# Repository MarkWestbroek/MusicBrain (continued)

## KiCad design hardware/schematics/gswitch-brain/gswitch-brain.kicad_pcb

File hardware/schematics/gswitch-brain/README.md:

# gswitch-brain — ESP32-S3-hoofdbord (Guitar Effect Switcher)

**Status**: rev 0.1 geroute — ERC 0, netcheck OK, DRC 0/0 (2026-07-12).
**Nog niet bestellen**: eerst `jlc_fix.py`-LCSC-match + fab-pakket + review.
Leidende spec: [`doc/guitar-switcher-spec.md`](../../../doc/guitar-switcher-spec.md).

*(Regenereren: `python hardware/kicad-generators/board_overview.py
<pcb> gswitch-brain-overzicht.json` — 3D-render via kicad-cli met
callouts in bord-mm.)*

## Wat dit bord is

Het "moederbord" van de switcher: ESP32-S3-WROOM-**1U** (U.FL-antenne →
SMA-bulkhead op de stalen kast), 12V **center-negatief** in (omkeer-P-FET +
polyfuse + SMAJ15A), buck 12→5V (TPS563201), AMS1117-3.3, USB-C voor
flash/debug (SS34-diode naar de 5V-rail: bord draait op USB zonder 12V),
MIDI-DIN in (H11L1) + uit (74HCT14-buffer op 5V), en 2× chain-poort
(74HCT541 → RJ45, met 100R-serieweerstanden en 10k/15k-spanningsdelers
voor de DATA_RET-teruglezing).

- Bord: 100 × 70 mm, 2-laags, GND-vlakken beide zijden.
- Randen: west DC + USB-C + debug-UART; noord 2× MIDI-DIN; zuid 2× RJ45;
  oost module + headers (OLED-I²C, 4 knoppen, encoder, 8× spare-GPIO).
- RESET- en BOOT-tactschakelaars naast de module; status-LED (IO42).

## GPIO-toewijzing (firmware-contract)

| Functie | GPIO | | Functie | GPIO |
|---|---|---|---|---|
| Chain A CLK/DATA/LATCH/EN | 4/5/6/7 | | I²C SDA/SCL | 10/13 |
| Chain B CLK/DATA/LATCH/EN | 15/16/17/18 | | MIDI RX/TX | 11/12 |
| DATA_RET A / B (in, 3V-deler) | 8 / 9 | | Knoppen 1-4 | 35/36/37/38 |
| Encoder A/B/SW | 39/40/41 | | Status-LED | 42 |
| Spare-header | 21/14/47/48/1/2 | | Debug-UART | 43/44 |

Strapping-pinnen IO0/IO3/IO45/IO46 zijn vrijgehouden (IO0 = BOOT-knop).

## Connector-pinouts

**J10/J11 — chain A/B (RJ45, naar loop8-borden).** ⚠️ Géén ethernet:
pin 4 voert 12 V!

| pin | 1 | 2 | 3 | 4 | 5 | 6 | 7 | 8 | scherm |
|---|---|---|---|---|---|---|---|---|---|
| functie | CLK | GND | DATA | **+12V** | GND | DRET (terug) | LATCH | EN | GND |

**J3 — MIDI UIT / J4 — MIDI IN (DIN-5, 180°).**

| DIN-pin | J3 (uit) | J4 (in) |
|---|---|---|
| 4 | +5V via 220R | stroomlus → H11L1 (220R) |
| 5 | data via 220R (HCT14-buffer) | stroomlus → H11L1 |
| 2 | GND | n.c. (galvanisch gescheiden) |
| scherm (E) | GND | GND |

**Headers (oostrand + debug).** Alle logica op de headers is 3,3 V.

| conn. | pin 1 → n |
|---|---|
| J5 OLED | GND · +3V3 · SCL · SDA |
| J6 knoppen | BTN1 · BTN2 · BTN3 · BTN4 · GND |
| J7 encoder | ENC_A · GND · ENC_B · ENC_SW · GND |
| J8 spare | +3V3 · GND · SPARE1…SPARE6 |
| J9 debug-UART | TX · RX · GND |

**J1 — voeding (2,1 mm barrel):** center = **GND**, mantel = +12 V
(center-negatief, pedaalconventie); ompoolbeveiligd (P-FET) en
polyfuse + TVS.

Diagrammen van álle connectoren staan in [`pinouts/`](pinouts/)
(gegenereerd met `pinout_svg.py` — leest netten uit het bordbestand,
loopt dus nooit uit de pas met het ontwerp).

## Onderdelen-notities

- **Module**: ESP32-S3-WROOM-**1U**-N8R2 — de -1U (U.FL) is verplicht in de
  metalen kast. EP-thermal-vias (0,2 mm) zijn uit de lib-footprint gefilterd
  (onder JLC-minimumboring); EP soldeert op het vlak.
- **MIDI-DIN**: CUI SDS-50J (footprint uit de maattekening, zie
  `doc/data-sheets/`-werkwijze). MIDI-out op 5V met 2×220R (spec-conform).
- **RJ45**: zelfde "56-klasse" afgeschermde 8P8C als loop8; schermen → GND
  (de brain is het sterpunt van de besturingsketen).
- **DC**: 2,1 mm barrel, **center-negatief** (pedaalconventie!).
- **Buck**: TPS563201 (SOT-23-6) + SRN4018 4,7 µH; FB 56k/10k (≈5,07 V);
  EN-deler 100k/33k vanaf 12V.
- **BOM/LCSC**: nog geen LCSC-velden — `jlc_fix.py` vóór fab-run.

## Bouwen

Zelfde pijplijn als loop8: `gen_gswitch_brain.py` → ERC/netcheck/DRC →
`export_dsn` → `gswitch_dsn_prep.py <dsn> --no-keepout --clearance-150` →
freerouting → generator opnieuw (SES native) → gnd_stitch/gnd_bridge → DRC 0/0.

### Routing-opbouw (rev 0.1)

- **Hand** (permanent geskipt bij SES-apply): +12V-ruggegraat, +3V3-snelweg
  (B, y=158,9), USB DP/DM/VBUS (bondlusjes + lanen, usb-netclass 0,1/0,15),
  CC2 (B-duik naast de DM-jog), en de **F-bus U2.7/8/9 → module p9/p10/p11**
  (B_DATA/B_LATCH/B_EN): lanen noord van de SW1/SW2-padrand, schuine
  eindstukjes de pads in.
- **Freerouting**: hoofdronde (r6) + hybride naruns (`--narun=<netten>` in
  `gswitch_dsn_prep.py`) voor netten die de hoofdronde niet haalde. De
  narun-SES wordt met `only=NARUN_NETS` over de hoofdronde gelegd.
- **GND**: 15 hand-stitchvia's + `gnd_stitch.json` (9 auto + 1 brugvia);
  de laatste brugplek is met een polygon-doorsnede (B-flard × F-hoofdvlak)
  bepaald op (163,78, 123,43).

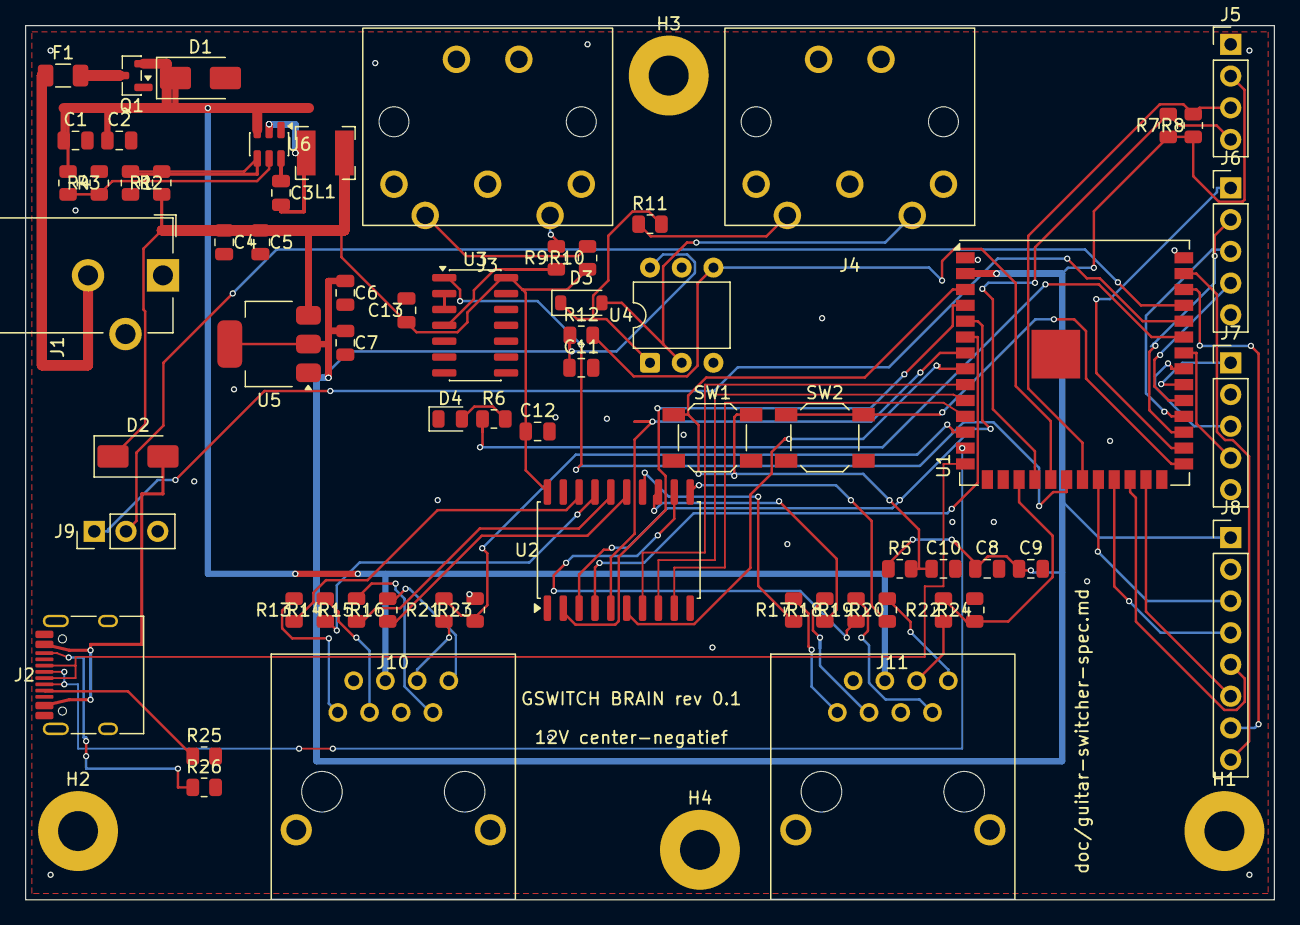
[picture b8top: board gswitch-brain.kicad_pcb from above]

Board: 2 copper layers, 100.0 x 70.0 mm, 69 parts (0 on the bottom side), 73 nets.

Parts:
C1: 10u; C_0805_2012Metric
C2, C3, C7, C9, C11, C12, C13: 100n; C_0805_2012Metric
C4, C5, C6, C8: 22u; C_0805_2012Metric
C10: 1u; C_0805_2012Metric
D1: SMAJ15A; D_SMA
D2: SS34; D_SMA
D3: 1N4148W; D_SOD-123
D4: LED-GN; LED_0805_2012Metric
F1: 1.1A; Fuse_1206_3216Metric
H1, H2, H3, H4: M3; MountingHole_3.2mm_M3_Pad
J1: DC-12V; BarrelJack_CUI_PJ-102AH_Horizontal
J2: USB-C; USB_C_Receptacle_HRO_TYPE-C-31-M-12
J3, J4: SDS-50J; DIN5_SDS50J
J5: OLED-I2C; PinHeader_1x04_P2.54mm_Vertical
J6: KNOPPEN; PinHeader_1x05_P2.54mm_Vertical
J7: ENCODER; PinHeader_1x05_P2.54mm_Vertical
J8: SPARE; PinHeader_1x08_P2.54mm_Vertical
J9: DEBUG; PinHeader_1x03_P2.54mm_Vertical
J10, J11: RJ45-S; RJ45_shielded
L1: 4u7; L_Bourns-SRN4018
Q1: AO3401; SOT-23
R1: 56k; R_0805_2012Metric
R2, R5, R21, R22: 10k; R_0805_2012Metric
R3: 100k; R_0805_2012Metric
R4: 33k; R_0805_2012Metric
R6, R12: 1k; R_0805_2012Metric
R7, R8: 4k7; R_0805_2012Metric
R9, R10, R11: 220R; R_0805_2012Metric
R13, R14, R15, R16, R17, R18, R19, R20: 100R; R_0805_2012Metric
R23, R24: 15k; R_0805_2012Metric
R25, R26: 5k1; R_0805_2012Metric
SW1: RESET; SW_SPST_SKQG_WithStem
SW2: BOOT; SW_SPST_SKQG_WithStem
U1: ESP32-S3-WROOM-1U-N8R2; ESP32-S3-WROOM-1U
U2: 74HCT541; SOIC-20W_7.5x12.8mm_P1.27mm
U3: 74HCT14; SOIC-14_3.9x8.7mm_P1.27mm
U4: H11L1; DIP-6_W7.62mm
U5: AMS1117-3.3; SOT-223-3_TabPin2
U6: TPS563201; SOT-23-6

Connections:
+3V3: C6.1, C7.1, C8.1, C9.1, C11.1, J5.2, J8.1, R5.1, R7.1, R8.1, R12.1, U1.2, U4.6, U5.2
+5V: C4.1, C5.1, C12.1, C13.1, D2.1, L1.2, R1.1, R10.1, U2.20, U3.14, U5.3
+12V: C1.1, C2.1, D1.1, J10.4, J11.4, Q1.2, R3.1, U6.3
/+12VRAW: F1.1, J1.2
/A_CLK: U1.4, U2.2
/A_CLK5: R13.1, U2.18
/A_CLKJ: J10.1, R13.2
/A_DATA: U1.5, U2.3
/A_DATA5: R14.1, U2.17
/A_DATAJ: J10.3, R14.2
/A_DRETJ: J10.6, R21.1
/A_EN: U1.7, U2.5
/A_EN5: R16.1, U2.15
/A_ENJ: J10.8, R16.2
/A_LATCH: U1.6, U2.4
/A_LATCH5: R15.1, U2.16
/A_LATCHJ: J10.7, R15.2
/BCK_EN: R3.2, R4.1, U6.5
/BOOT: SW2.1, U1.27
/BST: C3.1, U6.6
/BTN1: J6.1, U1.28
/BTN2: J6.2, U1.29
/BTN3: J6.3, U1.30
/BTN4: J6.4, U1.31
/B_CLK: U1.8, U2.6
/B_CLK5: R17.1, U2.14
/B_CLKJ: J11.1, R17.2
/B_DATA: U1.9, U2.7
/B_DATA5: R18.1, U2.13
/B_DATAJ: J11.3, R18.2
/B_DRETJ: J11.6, R22.1
/B_EN: U1.11, U2.9
/B_EN5: R20.1, U2.11
/B_ENJ: J11.8, R20.2
/B_LATCH: U1.10, U2.8
/B_LATCH5: R19.1, U2.12
/B_LATCHJ: J11.7, R19.2
/CC1: J2.A5, R25.1
/CC2: J2.B5, R26.1
/DBG_RX: J9.2, U1.37
/DBG_TX: J9.1, U1.36
/DRET_A: R21.2, R23.1, U1.12
/DRET_B: R22.2, R24.1, U1.17
/ENC_A: J7.1, U1.32
/ENC_B: J7.3, U1.33
/ENC_SW: J7.4, U1.34
/ESP_EN: C10.1, R5.2, SW1.1, U1.3
/FB: R1.2, R2.1, U6.4
/LEDK: D4.2, R6.2
/LEDK_A: R6.1, U1.35
/MIDI_RX: R12.2, U1.19, U4.4
/MIDI_TX: U1.20, U3.1
/MIN4: J4.4, R11.1
/MIN5: D3.2, J4.5, U4.2
/MINA: D3.1, R11.2, U4.1
/MOUT4: J3.4, R10.2
/MOUT5: J3.5, R9.2
/MTX5: R9.1, U3.4
/MTXN: U3.2, U3.3
/RAWF: F1.2, Q1.3
/SCL: J5.3, R8.2, U1.21
/SDA: J5.4, R7.2, U1.18
/SPARE1: J8.3, U1.22
/SPARE2: J8.4, U1.23
/SPARE3: J8.5, U1.24
/SPARE4: J8.6, U1.25
/SPARE5: J8.7, U1.38
/SPARE6: J8.8, U1.39
/SW: C3.2, L1.1, U6.2
/USB_DM: J2.A7, J2.B7, U1.13
/USB_DP: J2.A6, J2.B6, U1.14
/VBUS: D2.2, J2.A4, J2.A9, J2.B4, J2.B9
GND: C1.2, C2.2, C4.2, C5.2, C6.2, C7.2, C8.2, C9.2, C10.2, C11.2, C12.2, C13.2, D1.2, D4.1, H1.1, H2.1, H3.1, H4.1, J1.1, J2.A1, J2.A12, J2.B1, J2.B12, J2.SH, J3.2, J3.E, J4.E, J5.1, J6.5, J7.2, J7.5, J8.2, J9.3, J10.2, J10.5, J10.SH, J11.2, J11.5, J11.SH, Q1.1, R2.2, R4.2, R23.2, R24.2, R25.2, R26.2, SW1.2, SW2.2, U1.1, U1.40, U1.41, U2.1, U2.10, U2.19, U3.5, U3.7, U3.9, U3.11, U3.13, U4.5, U5.1, U6.1

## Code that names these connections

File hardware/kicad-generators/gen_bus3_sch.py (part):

"""Generate musicbrain-busboard.kicad_sch — v3 per doc/busboard-v3-plan.md.

v3 t.o.v. v2 (gen 2): slots 2x12 (audio-lijnen MCLK/BCLK/LRCLK gedeeld +
I2SD1-6 per slot, CONVST=pin 19), audiohub J24 (2x7), MIDI 2xIN/2xUIT (J22 =
TX7), USB-host-doorvoer J23 (2x5, volgorde-ongevoelig 1-op-1), R-78E5.0-1.0.
Verder v2-architectuur: 74HC154-CS-decoder, 74HC165-IRQ-keten, expansie J21,
CAN3, codec-header J17, TUNE-IN, delegate-UARTs.
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
# ---- v2-pintoewijzing (zie doc/busboard-v2-plan.md) ----
# links: symboolpin 2..24 = D0..D12? (2=D0,3=D1,4=D2,...,14=D12,16=D24..24=D32)
tpin_label(2, "DISP_CS")    # D0
tpin_label(3, "TUNE_T")     # D1  <- schmitt-uitgang TUNE
tpin_label(4, "LDAC")       # D2
tpin_label(5, "CSA0")       # D3
tpin_label(6, "CSA1")       # D4
tpin_label(7, "CSA2")       # D5
tpin_label(8, "CSA3")       # D6
tpin_label(9, "I2S_OUT")    # D7  OUT1A -> codec DIN
tpin_label(10, "I2S_IN")    # D8  IN1  <- codec DOUT
tpin_label(11, "CS_EN")     # D9  /E0 decoder
tpin_label(12, "D10")       # D10 vrij -> EXP
# 13 = MOSI via R2 (onder), 14 = MISO
tpin_label(14, "MISO")
tpin_label(16, "DISP_DC")   # D24
tpin_label(17, "DISP_RST")  # D25
tpin_label(18, "MOSI1")     # D26
tpin_label(19, "SCK1")      # D27
tpin_label(20, "MIDI_RX2")  # D28 RX7
tpin_label(21, "MIDI_TX2")  # D29 TX7 -> MIDI OUT2 (v3)
tpin_label(22, "CAN_RX")    # D30 CRX3
tpin_label(23, "CAN_TX")    # D31 CTX3
tpin_label(24, "D32")       # D32 vrij -> EXP
# rechts: 25=D33 ... 33=D41, 35=D13, 36..45=D14..D23
tpin_label(25, "D33")       # D33 vrij -> EXP
tpin_label(26, "MIDI_RX1")  # D34 RX8
tpin_label(27, "MIDI_TX")   # D35 TX8
tpin_label(28, "D36")
tpin_label(29, "D37")
tpin_label(30, "D38")
tpin_label(31, "D39")
tpin_label(32, "CONVST")    # D40 CONVST (busbrede sample-strobe, slotpin 19)
tpin_label(33, "SPARE2")    # D41 ADC_RESET
tpin_label(36, "DLG1_TX")   # D14 TX3
tpin_label(37, "DLG1_RX")   # D15 RX3
tpin_label(38, "DLG2_TX")   # D16 TX4
tpin_label(39, "DLG2_RX")   # D17 RX4
tpin_label(40, "SDA")       # D18
tpin_label(41, "SCL")       # D19
tpin_label(42, "LRCLK")     # D20 (busnet, slotpin 23)
tpin_label(43, "BCLK")      # D21 (busnet, slotpin 22)
tpin_label(44, "CODEC_RST") # D22 -> codec-header (bovenaan kolom)
tpin_label(45, "MCLK")      # D23 (busnet, slotpin 21)

# series R: MOSI (pin13, links) en SCLK (pin35, rechts)
x, y, _ = TEENSY_PINS[13]
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     ("17", "Y15", "output")]))
place_box("74HC154", "U4", "74HC154", 155, 62,
          "Package_SO:SOIC-24W_7.5x15.4mm_P1.27mm",
          {"23": ("label", "CSA0"), "22": ("label", "CSA1"),
           "21": ("label", "CSA2"), "20": ("label", "CSA3"),
           "18": ("label", "CS_EN"), "19": ("power", "power:GND"),
           "24": ("power", "power:+3V3"), "12": ("power", "power:GND"),
           "1": ("label", "CS1"), "2": ("label", "CS2"), "3": ("label", "CS3"),
           "4": ("label", "CS4"), "5": ("label", "CS5"), "6": ("label", "CS6"),
           "7": ("label", "CS7"), "8": ("label", "CS8"), "9": ("label", "CS9"),
           "10": ("label", "CS10"), "11": ("label", "CS11"), "13": ("label", "CS12"),
           "14": ("label", "CS13"), "15": ("label", "CS14"),
           "16": ("label", "IRQSTAT"), "17": ("nc",)})
cap100n("C10", 128, 62)

# ============ v2: IRQ-keten 2x 74HC165 + 1G125 ============
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place_box("74HC165", "U5", "74HC165", 200, 62,
          "Package_SO:SOIC-16_3.9x9.9mm_P1.27mm",
          {"1": ("label", "PL"), "2": ("label", "SCLK"),
           "15": ("power", "power:GND"), "10": ("label", "CHAIN"),
           "16": ("power", "power:+3V3"), "8": ("power", "power:GND"),
           "6": ("label", "IRQ5"), "5": ("label", "IRQ6"), "4": ("power", "power:GND"),
           "3": ("power", "power:GND"), "14": ("label", "IRQ1"), "13": ("label", "IRQ2"),
           "12": ("label", "IRQ3"), "11": ("label", "IRQ4"),
           "9": ("label", "Q7A"), "7": ("nc",)})
# U6 = tweede byte: IRQ7..IRQ12 (expansie) op D7..D2 — eigen ~PL-RC (PL2),
# zodat de puls lokaal bij U6 (noordstrook) wordt opgewekt i.p.v. het halve
# bord over te reizen; beide RC's hangen aan dezelfde IRQSTAT-flank.
place_box("74HC165", "U6", "74HC165", 200, 120,
          "Package_SO:SOIC-16_3.9x9.9mm_P1.27mm",
          {"1": ("label", "PL2"), "2": ("label", "SCLK"),
           "15": ("power", "power:GND"), "10": ("power", "power:GND"),
           "16": ("power", "power:+3V3"), "8": ("power", "power:GND"),
           "6": ("label", "IRQ7"), "5": ("label", "IRQ8"), "4": ("label", "IRQ9"),
           "3": ("label", "IRQ10"), "14": ("label", "IRQ11"), "13": ("label", "IRQ12"),
           "12": ("power", "power:GND"), "11": ("power", "power:GND"),
           "9": ("label", "CHAIN"), "7": ("nc",)})
libs_extra.append(boxdef("74LVC1G125",
    [("1", "~{OE}", "input"), ("2", "A", "input"),
     ("5", "VCC", "power_in"), ("3", "GND", "power_in")],
    [("4", "Y", "tri_state")], width=12.7))
place_box("74LVC1G125", "U7", "74LVC1G125", 155, 120,
          "Package_TO_SOT_SMD:SOT-23-5",
          {"1": ("label", "IRQSTAT"), "2": ("label", "Q7A"),
           "5": ("power", "power:+3V3"), "3": ("power", "power:GND"),
           "4": ("label", "MISO")})
cap100n("C15", 178, 62)   # U5
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cap100n("C17", 140, 120)  # U7/1G17's
# PL-RC (gatein8-recept): C9 220p vanaf IRQSTAT, R5 10k pull-up naar 3V3
(c9a, c9b) = rcomp("C9", "220p", 128, 138, 90)
wire(*c9a, c9a[0] - 3.81, c9a[1]); label("IRQSTAT", c9a[0] - 3.81, c9a[1])
wire(*c9b, c9b[0] + 3.81, c9b[1]); label("PL", c9b[0] + 3.81, c9b[1])
(r5t, r5b) = rcomp("R5", "10k", 128, 122, 0)
power("power:+3V3", *r5t)
wire(*r5b, r5b[0], r5b[1] + 2.54); label("PL", r5b[0], r5b[1] + 2.54)
# tweede PL-RC voor U6 (PL2)
(c18a, c18b) = rcomp("C18", "220p", 155, 138, 90)
wire(*c18a, c18a[0] - 3.81, c18a[1]); label("IRQSTAT", c18a[0] - 3.81, c18a[1])
wire(*c18b, c18b[0] + 3.81, c18b[1]); label("PL2", c18b[0] + 3.81, c18b[1])
(r33t, r33b) = rcomp("R33", "10k", 155, 122, 0)
power("power:+3V3", *r33t)
wire(*r33b, r33b[0], r33b[1] + 2.54); label("PL2", r33b[0], r33b[1] + 2.54)
# IRQ-pulldowns (12x 100k): gedefinieerd niveau voor lege slots/expansie
for k in range(12):
    xr = 88 + 5.08 * k
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          "Package_SO:SOIC-20W_7.5x12.8mm_P1.27mm",
          {"1": ("power", "power:+3V3"), "19": ("power", "power:GND"),
           "20": ("power", "power:+3V3"), "10": ("power", "power:GND"),
           "2": ("label", "SCLK"), "3": ("label", "MOSI"), "4": ("label", "LDAC"),
           "5": ("label", "CONVST"), "6": ("label", "SPARE2"),
           "7": ("power", "power:GND"), "8": ("power", "power:GND"),
           "9": ("power", "power:GND"),
           "18": ("label", "XSCLK0"), "17": ("label", "XMOSI0"),
           "16": ("label", "XLDAC0"), "15": ("label", "XCONVST0"),
           "14": ("label", "XRST0"), "13": ("nc",), "12": ("nc",), "11": ("nc",)})
cap100n("C11", 222, 100)
# 33R serie in de gebufferde lijnen naar de expansieheader
for k, (a, b) in enumerate((("XSCLK0", "XSCLK"), ("XMOSI0", "XMOSI"),
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
# MIDI OUT: 1G17-buffer + 10R/33R per 3V3-MIDI-spec
place_box("74LVC1G17", "U11", "74LVC1G17", 392, 158, "Package_TO_SOT_SMD:SOT-23-5",
          {"2": ("label", "MIDI_TX"), "5": ("power", "power:+3V3"),
           "3": ("power", "power:GND"), "4": ("label", "MOUT_Y"), "1": ("nc",)})
(l, r) = rcomp("R10", "10R", 414, 152, 90)
wire(*l, l[0] - 2.54, l[1]); label("MOUT_Y", l[0] - 2.54, l[1])
wire(*r, r[0] + 2.54, r[1]); label("MOUT5", r[0] + 2.54, r[1])
(l, r) = rcomp("R11", "33R", 414, 160, 90)
power("power:+3V3", l[0] - 1.27, l[1], vx=l[0] - 1.27, vy=l[1] - 3.302)
wire(*l, l[0] - 1.27, l[1])
wire(*r, r[0] + 2.54, r[1]); label("MOUT4", r[0] + 2.54, r[1])
component("Custom:Conn_01x03", "J15", "MIDI OUT", 438, 160, 0,
          "Connector_PinHeader_2.54mm:PinHeader_1x03_P2.54mm_Vertical",
          extra_props=rprop("J15", "MIDI OUT", 438, 160, 438, 160 - 6.35, 438, 160 + 6.35))
wire(430.38, 157.46, 425.3, 157.46); label("MOUT5", 425.3, 157.46)
wire(430.38, 160, 425.3, 160); label("MOUT4", 425.3, 160)
wire(430.38, 162.54, 427.84, 162.54); power("power:GND", 427.84, 162.54)

# ============ v3: MIDI OUT2 (TX7 -> 1G17 -> J22) ============
place_box("74LVC1G17", "U14", "74LVC1G17", 392, 182, "Package_TO_SOT_SMD:SOT-23-5",
          {"2": ("label", "MIDI_TX2"), "5": ("power", "power:+3V3"),
           "3": ("power", "power:GND"), "4": ("label", "MOUT2_Y"), "1": ("nc",)})
(l, r) = rcomp("R34", "10R", 414, 176, 90)
wire(*l, l[0] - 2.54, l[1]); label("MOUT2_Y", l[0] - 2.54, l[1])
wire(*r, r[0] + 2.54, r[1]); label("MOUT2_5", r[0] + 2.54, r[1])
(l, r) = rcomp("R35", "33R", 414, 184, 90)
power("power:+3V3", l[0] - 1.27, l[1], vx=l[0] - 1.27, vy=l[1] - 3.302)
wire(*l, l[0] - 1.27, l[1])
wire(*r, r[0] + 2.54, r[1]); label("MOUT2_4", r[0] + 2.54, r[1])
component("Custom:Conn_01x03", "J22", "MIDI OUT2", 438, 184, 0,
          "Connector_PinHeader_2.54mm:PinHeader_1x03_P2.54mm_Vertical",
          extra_props=rprop("J22", "MIDI OUT2", 438, 184, 438, 184 - 6.35, 438, 184 + 6.35))
wire(430.38, 181.46, 425.3, 181.46); label("MOUT2_5", 425.3, 181.46)
wire(430.38, 184, 425.3, 184); label("MOUT2_4", 425.3, 184)
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
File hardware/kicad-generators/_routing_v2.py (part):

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    jx, jy = P['J21'][jpin]
    ry = CS_ROWY_[net]
    T(net, 'F.Cu', SW, (colx, ry), (jx, ry), (jx, jy))
# IRQSTAT: pin16 -> kanaalkolom x 43.9 (F, met B-hop over de DISP-rijen heen
# voor de noordtak) -> C9 + U7 (zuid) en C18 (noordoost)
px, py = P['U4']['16']
T('/IRQSTAT', 'F.Cu', SW, (px, py), (43.9, py), (43.9, 92.5),
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  (P['R5']['2'][0], 94.6), (P['R5']['2'][0], P['R5']['2'][1]))
T('/PL', 'F.Cu', SW, (P['C9']['2'][0], 94.6), (P['U5']['1'][0], 94.6),
  (P['U5']['1'][0], P['U5']['1'][1]))
# PL2: C18.2 + R33.2 -> U6 pin1
T('/PL2', 'F.Cu', SW, (P['C18']['2'][0], P['C18']['2'][1]),
  (P['R33']['2'][0], P['C18']['2'][1]), (P['R33']['2'][0], P['R33']['2'][1]))
T('/PL2', 'F.Cu', SW, (P['R33']['2'][0], P['R33']['2'][1]),
  (P['U6']['1'][0], P['R33']['2'][1]), (P['U6']['1'][0], P['U6']['1'][1]))

# ---- IRQ-keten zuidwest ----
# IRQ1-4: zuidrij-pinnen (3-6) recht omhoog naar hun lane
for net, pin in (('/IRQ1', '6'), ('/IRQ2', '5'), ('/IRQ3', '4'), ('/IRQ4', '3')):
    px, py = P['U5'][pin]
    T(net, 'F.Cu', SW, (px, py), (px, lane_y(net)))
    V(net, px, lane_y(net))
# IRQ5/6: noordrij-pinnen (14/13) via pad-gap-kolommen x 33.2 / 34.465
T('/IRQ5', 'F.Cu', SW, (P['U5']['14'][0], P['U5']['14'][1]), (P['U5']['14'][0], 97.5),
  (33.2, 97.5), (33.2, lane_y('/IRQ5')))
V('/IRQ5', 33.2, lane_y('/IRQ5'))
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    p1 = P[ref]['1']
    T(net, 'F.Cu', SW, (colx, 103.7 if colx > 34.6 else lane_y(net)),
      (colx, p1[1] - 0.55), (p1[0], p1[1]))
# Q7A: U5 pin9 -> rij y 96.9 -> kolom x 46.6 -> rij y 85 -> U7 pin2
T('/Q7A', 'F.Cu', SW, (P['U5']['9'][0], P['U5']['9'][1]), (P['U5']['9'][0], 96.9),
  (46.6, 96.9), (46.6, 85.0), (P['U7']['2'][0], 85.0), (P['U7']['2'][0], P['U7']['2'][1]))
# CHAIN: U6 pin10 -> F-rij y 18.3 -> kanaal (B/F-hops) -> U5 pin10
T('/CHAIN', 'F.Cu', SW, (P['U6']['10'][0], P['U6']['10'][1]), (P['U6']['10'][0], 18.3),
  (41.89, 18.3), (41.89, 26.0))
V('/CHAIN', 41.89, 26.0)
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    ly = lane_y(net)
    T(net, 'F.Cu', SW, (colx, ly), (colx, rowy), (px, rowy), (px, py))
    V(net, colx, ly)
XPINS = [('/XSCLK0', '18', 'R16', '/XSCLK', '15'), ('/XMOSI0', '17', 'R17', '/XMOSI', '17'),
         ('/XLDAC0', '16', 'R18', '/XLDAC', '19'), ('/XCONVST0', '15', 'R19', '/XCONVST', '21'),
         ('/XRST0', '14', 'R20', '/XRST', '23')]
for k, (net0, pin, rref, net1, jpin) in enumerate(XPINS):
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    ly = lane_y(net)
    V(net, colx, ly)
    T(net, 'F.Cu', SW, (colx, ly), (colx, 17.8), (jx + 0.85, 17.8), (jx, 18.6), (jx, jy))
# IRQ7-10: J21 noordrij -> B-rijen -> U6 zuidrij-pinnen (vias bij de pads)
IRQ_NA = [('/IRQ7', '2', '6', 20.3), ('/IRQ8', '4', '5', 20.9),
          ('/IRQ9', '6', '4', 21.5), ('/IRQ10', '8', '3', 23.8)]
for net, jpin, upin, rowy in IRQ_NA:
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    T(net, 'B.Cu', SW, (jx, jy), (jx, rowy), (ux, rowy))
    V(net, ux, rowy)
    T(net, 'F.Cu', SW, (ux, rowy), (ux, uy))
# IRQ11/12: J21 -> B noordom -> U6 noordrij-pinnen
IRQ_NB = [('/IRQ11', '10', '14', 119.0, 11.3), ('/IRQ12', '12', '13', 121.5, 11.9)]
for net, jpin, upin, jogx, rowy in IRQ_NB:
    jx, jy = P['J21'][jpin]
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T('/CAN_RS', 'F.Cu', SW, (P['U12']['8'][0], P['U12']['8'][1]),
  (P['U12']['8'][0] + 0.8, P['U12']['8'][1] - 0.8), (P['R13']['1'][0], 99.3),
  (P['R13']['1'][0], P['R13']['1'][1]))
# CANH: pin7 -> B-hop over de +12V-kolom -> R12.1; verder -> J16.2
T('/CANH', 'F.Cu', SW, (P['U12']['7'][0], P['U12']['7'][1]), (89.8, P['U12']['7'][1]),
  (89.8, 104.0), (92.775, 104.0))
V('/CANH', 92.9, 104.0)
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# CAN_TRM: R12.2 -> JP1.1
T('/CAN_TRM', 'F.Cu', SW, (P['R12']['2'][0], P['R12']['2'][1]),
  (P['JP1']['1'][0], P['R12']['2'][1] + 0.0), (P['JP1']['1'][0], P['JP1']['1'][1]))
# CANL: pin6 -> B-hop -> JP1.2 -> J16.3
T('/CANL', 'F.Cu', SW, (P['U12']['6'][0], P['U12']['6'][1]), (90.5, P['U12']['6'][1]),
  (90.5, 105.2), (92.775, 105.2))
V('/CANL', 92.9, 105.2)
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
# ---- codec noordwest (J17) ----
# oost-groep: pads 44/45/43/42 -> F-jogs -> F-kolommen -> B-jogs -> B-kolommen
# -> B-rijen -> J17 even pinnen (pinvolgorde: 2=RST? nee: 2=CODEC_RST zit in map)
CODEC_E = [
    # net, teensy-pad, mid_y, fcol, bjog_y, bcol, row_y, j17-pin
    ('/MCLK1', '45', 46.35, 46.6, 44.8, 54.59, 17.15, '4'),
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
